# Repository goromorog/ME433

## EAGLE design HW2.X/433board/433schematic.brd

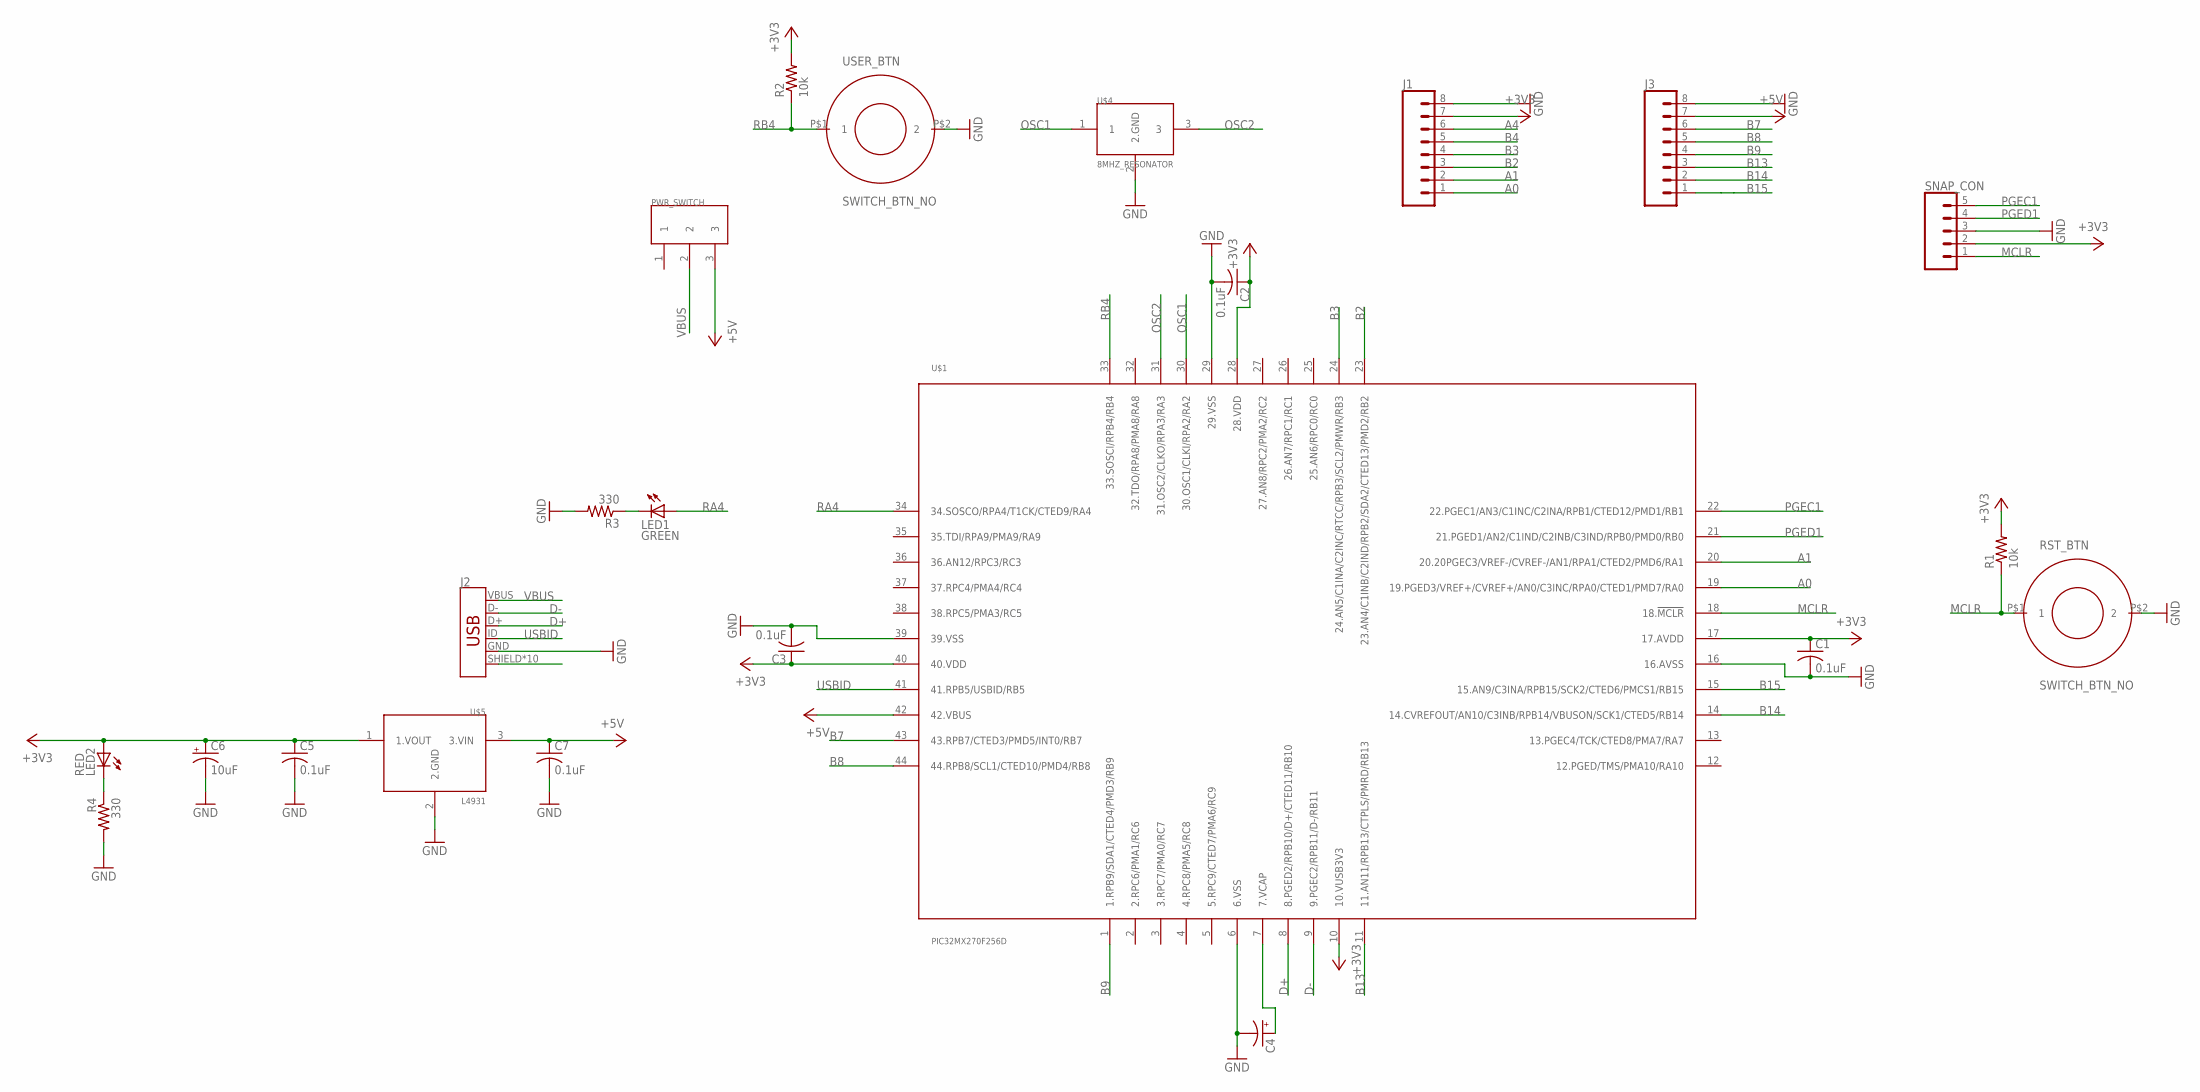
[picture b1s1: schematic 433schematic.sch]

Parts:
C1, C2, C3, C5, C7: 0.1uF; C025-024X044
C4: CPOL-USB45181A; B45181A
C6: 10uF; B45181A
J1, J3: CONN_08"; 1X08
J2: USB_MICRO-B_HALF_PTH_MILL; USB-MICROB-PTH-MILL
LED1: GREEN; LED3MM
LED2: RED; LED3MM
PWR_SWITCH: SLIDE_SWITCH
R1, R2: 10k; 0204/5
R3, R4: 330; 0204/5
RST_BTN: SWITCH_BTN_NO; BTN_2
SNAP_CON: CONN_05; 1X05
U$1: PIC32MX270F256D; TQFP44
U$4: 8MHZ_RESONATOR
U$5: L4931; TO92
USER_BTN: SWITCH_BTN_NO; BTN_2

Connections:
+3V3: C1.1, C2.1, C3.1, C5.1, C6.+, J1.7, LED2.A, R1.2, R2.2, SNAP_CON.2, U$1.10 (10.VUSB3V3), U$1.17 (17.AVDD), U$1.28 (28.VDD), U$1.40 (40.VDD), U$5.1 (1.VOUT)
+5V: C7.1, J3.7, PWR_SWITCH.3, U$1.42 (42.VBUS), U$5.3 (3.VIN)
A0: J1.1, U$1.19 (19.PGED3/VREF+/CVREF+/AN0/C3INC/RPA0/CT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)
A1: J1.2, U$1.20 (20.20PGEC3/VREF-/CVREF-/AN1/RPA1/CTED2/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)
A4: J1.6
B2: J1.3, U$1.23 (23.AN4/C1INB/C2IND/RPB2/SDA2/CTED13/PMD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)
B3: J1.4, U$1.24 (24.AN5/C1INA/C2INC/RTCC/RPB3/SCL2/PMWR/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)
B4: J1.5
B7: J3.6, U$1.43 (43.RPB7/CTED3/PMD5/INT0/RB7)
B8: J3.5, U$1.44 (44.RPB8/SCL1/CTED10/PMD4/RB8)
B9: J3.4, U$1.1 (1.RPB9/SDA1/CTED4/PMD3/RB9)
B13: J3.3, U$1.11 (11.AN11/RPB13/CTPLS/PMRD/RB13)
B14: J3.2, U$1.14 (14.CVREFOUT/AN10/C3INB/RPB14/VBUSON/SCK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)
B15: J3.1, U$1.15 (15.AN9/C3INA/RPB15/SCK2/CTED6/PMCS1/RB15)
D+: J2.D+, U$1.8 (8.PGED2/RPB10/D+/CTED11/RB10)
D-: J2.D-, U$1.9 (9.PGEC2/RPB11/D-/RB11)
GND: C1.2, C2.2, C3.2, C4.-, C5.2, C6.-, C7.2, J1.8, J2.GND, J3.8, R3.2, R4.2, RST_BTN.P$2 (2), SNAP_CON.3, U$1.6 (6.VSS), U$1.16 (16.AVSS), U$1.29 (29.VSS), U$1.39 (39.VSS), U$4.2 (2.GND), U$5.2 (2.GND), USER_BTN.P$2 (2)
MCLR: R1.1, RST_BTN.P$1 (1), SNAP_CON.1, U$1.18 (18.!MCLR!)
unnamed: LED1.K (C), R3.1
unnamed: LED2.K (C), R4.1
unnamed: C4.+, U$1.7 (7.VCAP)
unnamed: J2.SHIELD, J2.SHIELD2 (SHIELD), J2.SHIELD3 (SHIELD), J2.SHIELD4 (SHIELD), J2.SHIELD5 (SHIELD), J2.SHIELD6 (SHIELD), J2.SHIELD7 (SHIELD), J2.SHIELD8 (SHIELD), J2.SHIELD9 (SHIELD), J2.SHIELD10 (SHIELD)
OSC1: U$1.30 (30.OSC1/CLKI/RPA2/RA2), U$4.1
OSC2: U$1.31 (31.OSC2/CLKO/RPA3/RA3), U$4.3
PGEC1: SNAP_CON.5, U$1.22 (22.PGEC1/AN3/C1INC/C2INA/RPB1/CTED12/PM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)
PGED1: SNAP_CON.4, U$1.21 (21.PGED1/AN2/C1IND/C2INB/C3IND/RPB0/PMD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)
RA4: LED1.A, U$1.34 (34.SOSCO/RPA4/T1CK/CTED9/RA4)
RB4: R2.1, U$1.33 (33.SOSCI/RPB4/RB4), USER_BTN.P$1 (1)
USBID: J2.ID, U$1.41 (41.RPB5/USBID/RB5)
VBUS: J2.VBUS, PWR_SWITCH.2

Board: 2 copper layers, 23 parts (0 on the bottom side), 28 nets, no tracks yet.

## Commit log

2019-04-02 hw1 setup
2019-04-04 creating main
2019-04-05 nscope screenshots
2019-04-15 Create 433lib.l#3
2019-04-15 Create 433lib.l#1
2019-04-15 Create 433lib.l#9
2019-04-15 Create 433lib.l#8
2019-04-15 Create 433lib.l#7
2019-04-15 Create 433schematic.s#1
2019-04-18 Create 433lib.l#6
2019-04-19 starting spi with template
2019-04-19 v1 of hw4
2019-04-19 debugging spi
2019-04-19 more debugging spi
2019-04-19 working spi
2019-04-20 final spi hw4
2019-04-23 initial i2c attempts
2019-04-24 first i2c build
2019-04-24 final hw5
2019-04-24 lcd finished drawLetter
2019-04-25 LCD draw letter working
2019-04-28 final hw6 lcd
2019-04-28 initial imu code
2019-04-28 hw7 inits
2019-04-28 function to read multiple registers
2019-04-29 debugging imu
2019-04-29 failed attempts at debugging
2019-04-30 working sliding bar in x dir
2019-05-01 Final HW7
2019-05-02 init harmony for hw8
2019-05-02 Final HW8
2019-05-05 working touchscreen
2019-05-06 final hw9
2019-05-19 initializing usb
2019-05-19 imu data sent to computer
2019-05-19 final working usb communication
2019-05-21 hw11 using same starting code as hw10
2019-05-21 commenting out irrelevant code
2019-05-21 maf completed
2019-05-21 first try of filters
2019-05-21 final hw10
2019-05-21 Revert "final hw10"
    This reverts commit 1e2661275eea9c16b28112c00a48eda1540a21ca.
2019-05-21 Revert "Revert "final hw10""
    This reverts commit 5a386718581acf3f85eaf96a3b30d8a241f8676d.
2019-05-28 configuring hw12 mouse hid
2019-05-28 finished box and wheel
2019-05-28 configuring hid
2019-05-28 cad and 3d prints
2019-06-06 pictures for hw13
2019-06-08 building code to test for hw12
2019-06-08 working hw12
2019-06-09 initialize hw15
2019-06-09 finished lcd graphing
2019-06-09 hw15 with interrupts
2019-06-11 all CAD
2019-06-11 hw13 pics
2019-06-13 final line following program
2019-06-13 added pictures

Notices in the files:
parts and their libraries:
SparkFun-Connectors: Licensing: Creative Commons ShareAlike 4.0 International - https://creativecommons.org/licenses/by-sa/4.0
